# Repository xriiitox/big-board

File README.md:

# big-board

I wanted to make this keyboard to gain KiCAD experience and work on a larger project that included more difficult CAD.  
This was the first large-scale PCB I've worked on.  
The routing was very difficult, and it forced me to learn how to use vias correctly lol  

Personally, I don't really need much from a keyboard, so I tried to keep it simple with a minimalist design:
* No RGB
* No OLED Display
* No Rotary Encoders

Images: 

BOM:  
| Item     | Quantity | $/item | Total (inc. shipping) | Link |
| -------- | -------- | ------ | --------------------- | ---- |
| 1N4148   | 70       | 0.0292 | ~$10.50               | https://www.digikey.com/en/products/detail/onsemi/1N4148/458603 |
| Switches | 80       | 2.30   | ~$23.40 | https://milktooth.com/products/switches/milky-yellow-pro |
| Keycaps  | 1        | 0.99   | ~$1.06  | https://www.aliexpress.us/item/3256807135386098.html  |
| Stabs    | 1 set    | 16.99  | $16.99 | https://www.amazon.com/DUROCK-Stabilizers-Stabilizer-Pre-Clipped-Mechanical/dp/B0B2RTQ1C2 |
| M3 Screws| 1 box    | 9.99   | $9.99 | https://www.amazon.com/Assortment-Stainless-Replacement-Machine-Fastener/dp/B0BMQFHDBH |
| Orpheus Pico | 1 | 0.00 | 0.00 | N/A

PCB:

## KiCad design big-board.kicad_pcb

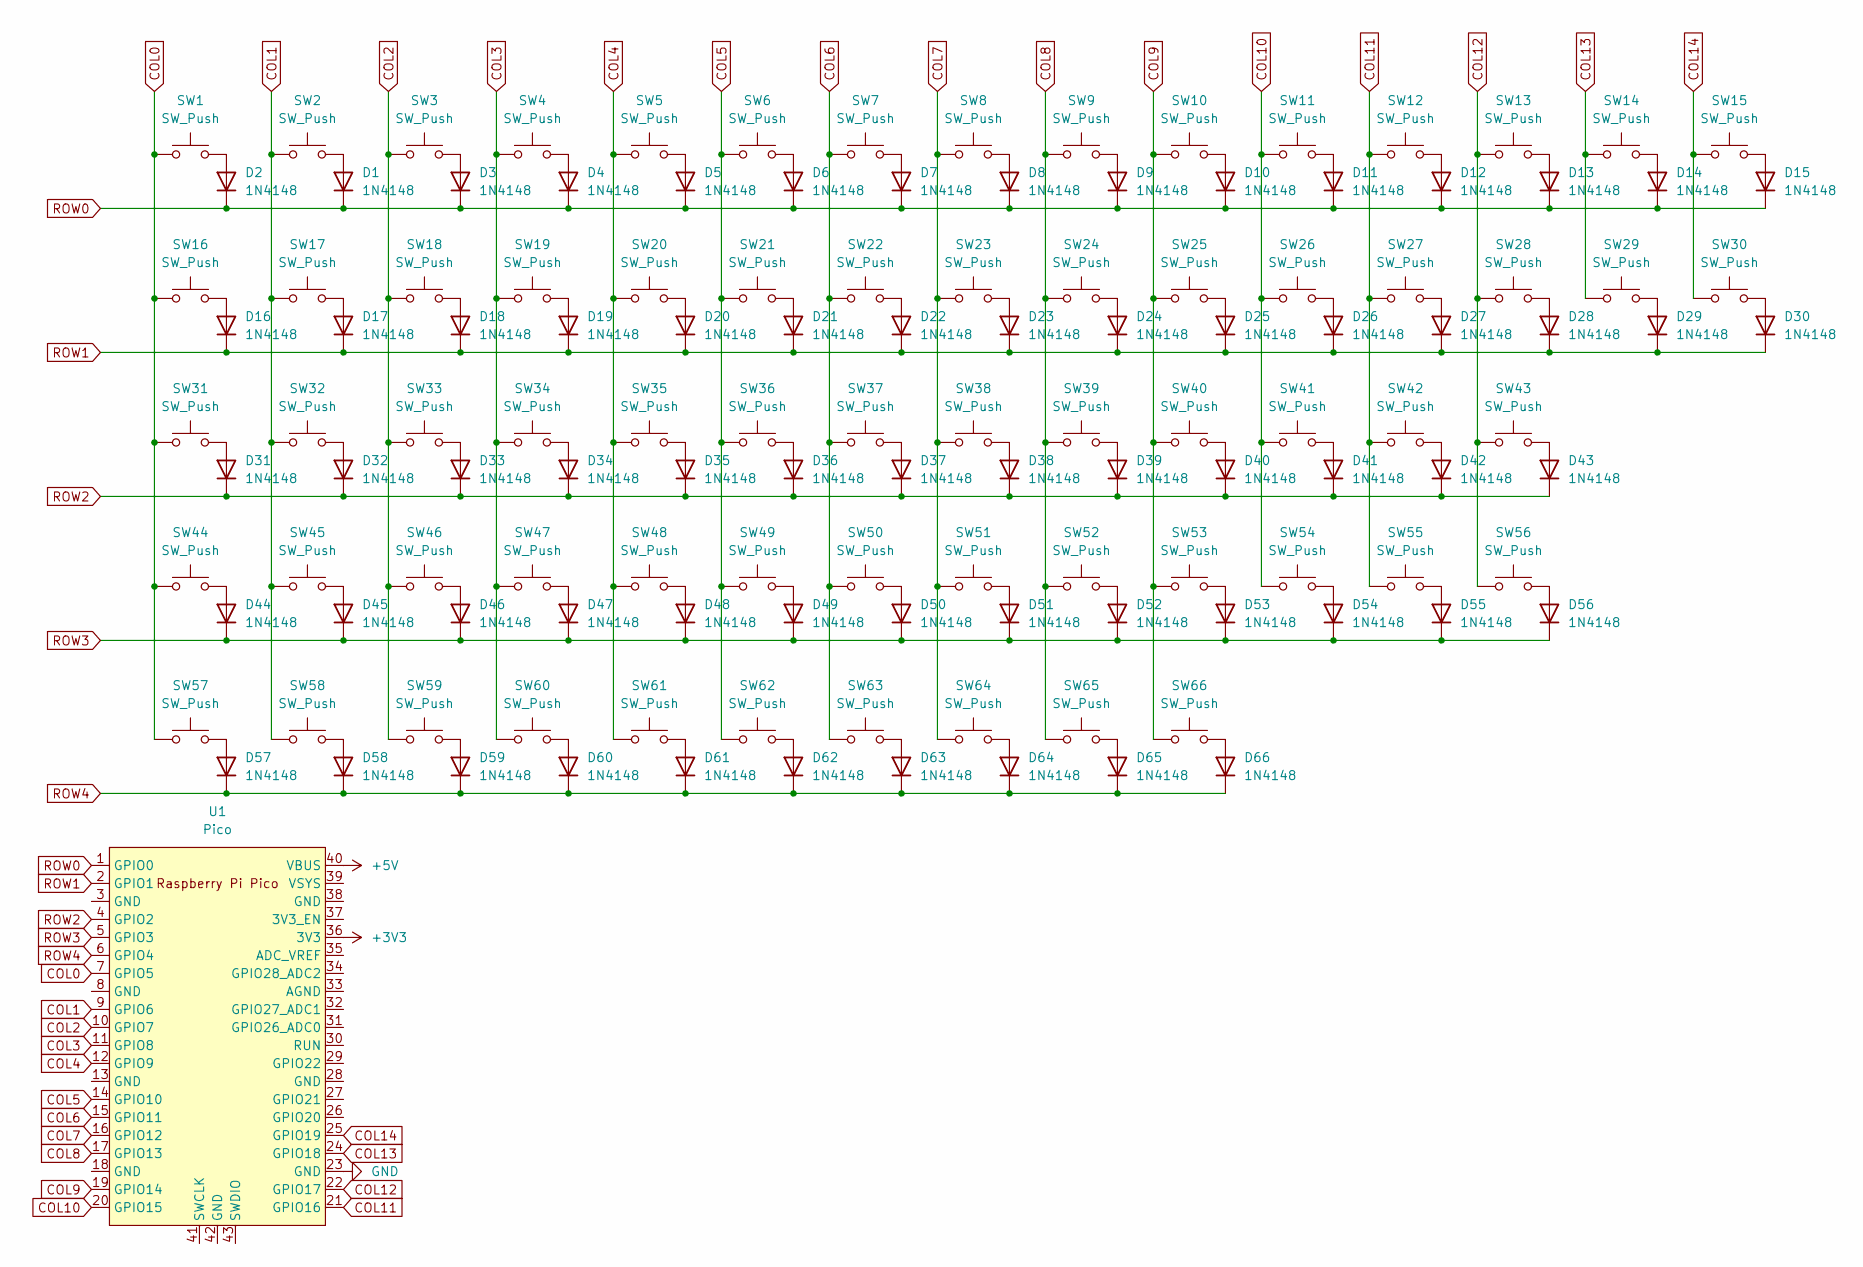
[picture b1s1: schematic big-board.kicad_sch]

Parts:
D1, D2, D3, D4, D5, D6, D7, D8, D9, D10, D11, D12, D13, D14, D15, D16, D17, D18, D19, D20, D21, D22, D23, D24, D25, D26, D27, D28, D29, D30, D31, D32, D33, D34, D35, D36, D37, D38, D39, D40, D41, D42, D43, D44, D45, D46, D47, D48, D49, D50, D51, D52, D53, D54, D55, D56, D57, D58, D59, D60, D61, D62, D63, D64, D65, D66: 1N4148; D_DO-35_SOD27_P7.62mm_Horizontal
SW1, SW2, SW3, SW4, SW5, SW6, SW7, SW8, SW9, SW10, SW11, SW12, SW13, SW15, SW17, SW18, SW19, SW20, SW21, SW22, SW23, SW24, SW25, SW26, SW27, SW28, SW30, SW32, SW33, SW34, SW35, SW36, SW37, SW38, SW39, SW40, SW41, SW42, SW45, SW46, SW47, SW48, SW49, SW50, SW51, SW52, SW53, SW54, SW56, SW58, SW64, SW65, SW66: SW_Push; MX-Solderable-1U
SW14: SW_Push; MX-Solderable-2U
SW16, SW29: SW_Push; MX-Solderable-1.5U
SW31: SW_Push; MX-Solderable-1.75U
SW43, SW44, SW55: SW_Push; MX-Solderable-2.25U
SW57, SW59, SW61, SW62, SW63: SW_Push; MX-Solderable-1.25U
SW60: SW_Push; MX-Solderable-6.25U
U1: Pico; RPi_Pico_SMD_TH

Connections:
+3V3: U1.36 (3V3)
+5V: U1.40 (VBUS)
COL0: SW1.1, SW16.1, SW31.1, SW44.1, SW57.1, U1.7 (GPIO5)
COL1: SW2.1, SW17.1, SW32.1, SW45.1, SW58.1, U1.9 (GPIO6)
COL2: SW3.1, SW18.1, SW33.1, SW46.1, SW59.1, U1.10 (GPIO7)
COL3: SW4.1, SW19.1, SW34.1, SW47.1, SW60.1, U1.11 (GPIO8)
COL4: SW5.1, SW20.1, SW35.1, SW48.1, SW61.1, U1.12 (GPIO9)
COL5: SW6.1, SW21.1, SW36.1, SW49.1, SW62.1, U1.14 (GPIO10)
COL6: SW7.1, SW22.1, SW37.1, SW50.1, SW63.1, U1.15 (GPIO11)
COL7: SW8.1, SW23.1, SW38.1, SW51.1, SW64.1, U1.16 (GPIO12)
COL8: SW9.1, SW24.1, SW39.1, SW52.1, SW65.1, U1.17 (GPIO13)
COL9: SW10.1, SW25.1, SW40.1, SW53.1, SW66.1, U1.19 (GPIO14)
COL10: SW11.1, SW26.1, SW41.1, SW54.1, U1.20 (GPIO15)
COL11: SW12.1, SW27.1, SW42.1, SW55.1, U1.21 (GPIO16)
COL12: SW13.1, SW28.1, SW43.1, SW56.1, U1.22 (GPIO17)
COL13: SW14.1, SW29.1, U1.24 (GPIO18)
COL14: SW15.1, SW30.1, U1.25 (GPIO19)
GND: U1.23 (GND)
unnamed: D1.2 (A), SW2.2
unnamed: D2.2 (A), SW1.2
unnamed: D3.2 (A), SW3.2
unnamed: D4.2 (A), SW4.2
unnamed: D5.2 (A), SW5.2
unnamed: D6.2 (A), SW6.2
unnamed: D7.2 (A), SW7.2
unnamed: D8.2 (A), SW8.2
unnamed: D9.2 (A), SW9.2
unnamed: D10.2 (A), SW10.2
unnamed: D11.2 (A), SW11.2
unnamed: D12.2 (A), SW12.2
unnamed: D13.2 (A), SW13.2
unnamed: D14.2 (A), SW14.2
unnamed: D15.2 (A), SW15.2
unnamed: D16.2 (A), SW16.2
unnamed: D17.2 (A), SW17.2
unnamed: D18.2 (A), SW18.2
unnamed: D19.2 (A), SW19.2
unnamed: D20.2 (A), SW20.2
unnamed: D21.2 (A), SW21.2
unnamed: D22.2 (A), SW22.2
unnamed: D23.2 (A), SW23.2
unnamed: D24.2 (A), SW24.2
unnamed: D25.2 (A), SW25.2
unnamed: D26.2 (A), SW26.2
unnamed: D27.2 (A), SW27.2
unnamed: D28.2 (A), SW28.2
unnamed: D29.2 (A), SW29.2
unnamed: D30.2 (A), SW30.2
unnamed: D31.2 (A), SW31.2
unnamed: D32.2 (A), SW32.2
unnamed: D33.2 (A), SW33.2
unnamed: D34.2 (A), SW34.2
unnamed: D35.2 (A), SW35.2
unnamed: D36.2 (A), SW36.2
unnamed: D37.2 (A), SW37.2
unnamed: D38.2 (A), SW38.2
unnamed: D39.2 (A), SW39.2
unnamed: D40.2 (A), SW40.2
unnamed: D41.2 (A), SW41.2
unnamed: D42.2 (A), SW42.2
unnamed: D43.2 (A), SW43.2
unnamed: D44.2 (A), SW44.2
unnamed: D45.2 (A), SW45.2
unnamed: D46.2 (A), SW46.2
unnamed: D47.2 (A), SW47.2
unnamed: D48.2 (A), SW48.2
unnamed: D49.2 (A), SW49.2
unnamed: D50.2 (A), SW50.2
unnamed: D51.2 (A), SW51.2
unnamed: D52.2 (A), SW52.2
unnamed: D53.2 (A), SW53.2
unnamed: D54.2 (A), SW54.2
unnamed: D55.2 (A), SW55.2
unnamed: D56.2 (A), SW56.2
unnamed: D57.2 (A), SW57.2
unnamed: D58.2 (A), SW58.2
unnamed: D59.2 (A), SW59.2
unnamed: D60.2 (A), SW60.2
unnamed: D61.2 (A), SW61.2
unnamed: D62.2 (A), SW62.2
unnamed: D63.2 (A), SW63.2
unnamed: D64.2 (A), SW64.2
unnamed: D65.2 (A), SW65.2
unnamed: D66.2 (A), SW66.2
ROW0: D1.1 (K), D2.1 (K), D3.1 (K), D4.1 (K), D5.1 (K), D6.1 (K), D7.1 (K), D8.1 (K), D9.1 (K), D10.1 (K), D11.1 (K), D12.1 (K), D13.1 (K), D14.1 (K), D15.1 (K), U1.1 (GPIO0)
ROW1: D16.1 (K), D17.1 (K), D18.1 (K), D19.1 (K), D20.1 (K), D21.1 (K), D22.1 (K), D23.1 (K), D24.1 (K), D25.1 (K), D26.1 (K), D27.1 (K), D28.1 (K), D29.1 (K), D30.1 (K), U1.2 (GPIO1)
ROW2: D31.1 (K), D32.1 (K), D33.1 (K), D34.1 (K), D35.1 (K), D36.1 (K), D37.1 (K), D38.1 (K), D39.1 (K), D40.1 (K), D41.1 (K), D42.1 (K), D43.1 (K), U1.4 (GPIO2)
ROW3: D44.1 (K), D45.1 (K), D46.1 (K), D47.1 (K), D48.1 (K), D49.1 (K), D50.1 (K), D51.1 (K), D52.1 (K), D53.1 (K), D54.1 (K), D55.1 (K), D56.1 (K), U1.5 (GPIO3)
ROW4: D57.1 (K), D58.1 (K), D59.1 (K), D60.1 (K), D61.1 (K), D62.1 (K), D63.1 (K), D64.1 (K), D65.1 (K), D66.1 (K), U1.6 (GPIO4)

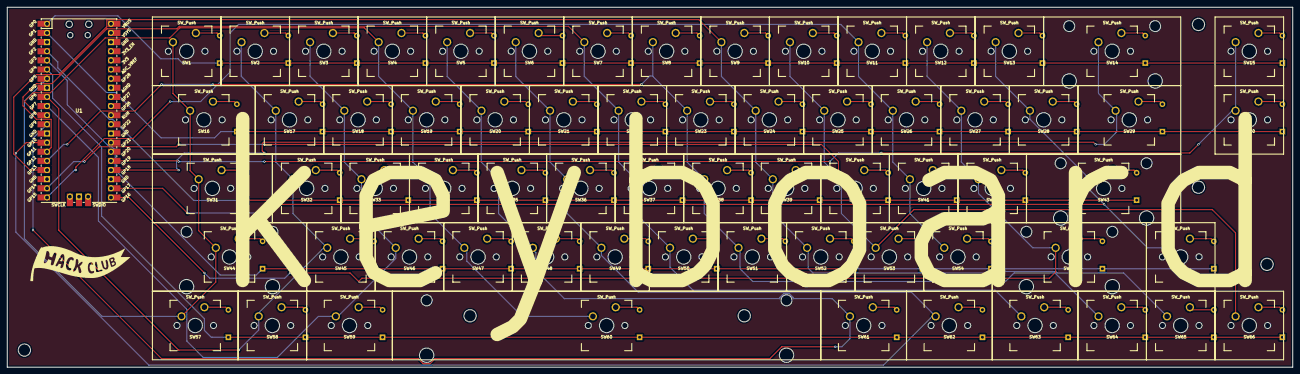
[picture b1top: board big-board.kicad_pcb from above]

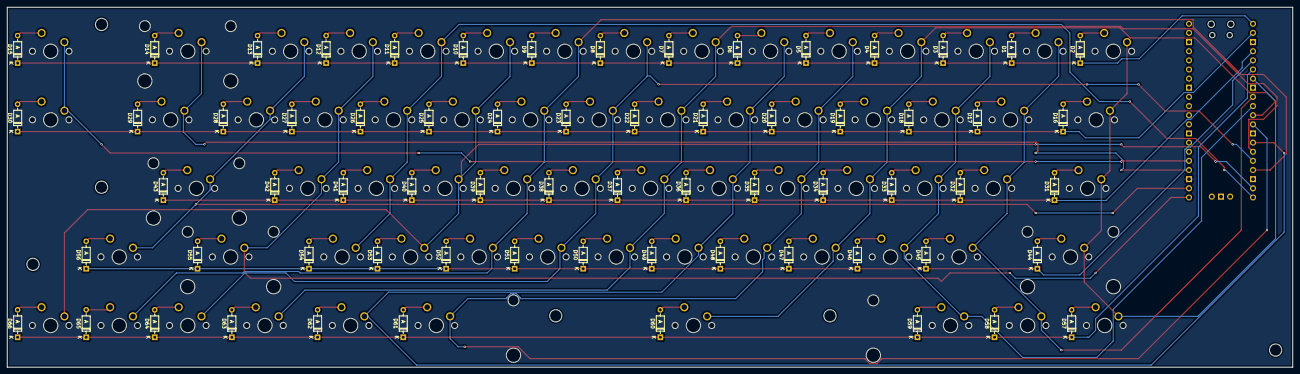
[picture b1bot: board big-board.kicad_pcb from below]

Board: 2 copper layers, 357.2 x 100.0 mm, 133 parts (66 on the bottom side), 86 nets.

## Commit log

2025-02-21 start routing
2025-02-21 keep routing
2025-02-28 more pcb routing
2025-03-01 hole
2025-03-01 finish pcb
2025-03-03 silkscreen stuff
2025-03-15 fix pcb and generate 3d model
2025-03-16 wrong gitignore
2025-03-16 separate folders and add CAD
2025-03-16 reorganize, add BOM, add gerbers
2025-03-16 add images
2025-06-06 fix BOM.md
2025-06-06 add full keyboard img
